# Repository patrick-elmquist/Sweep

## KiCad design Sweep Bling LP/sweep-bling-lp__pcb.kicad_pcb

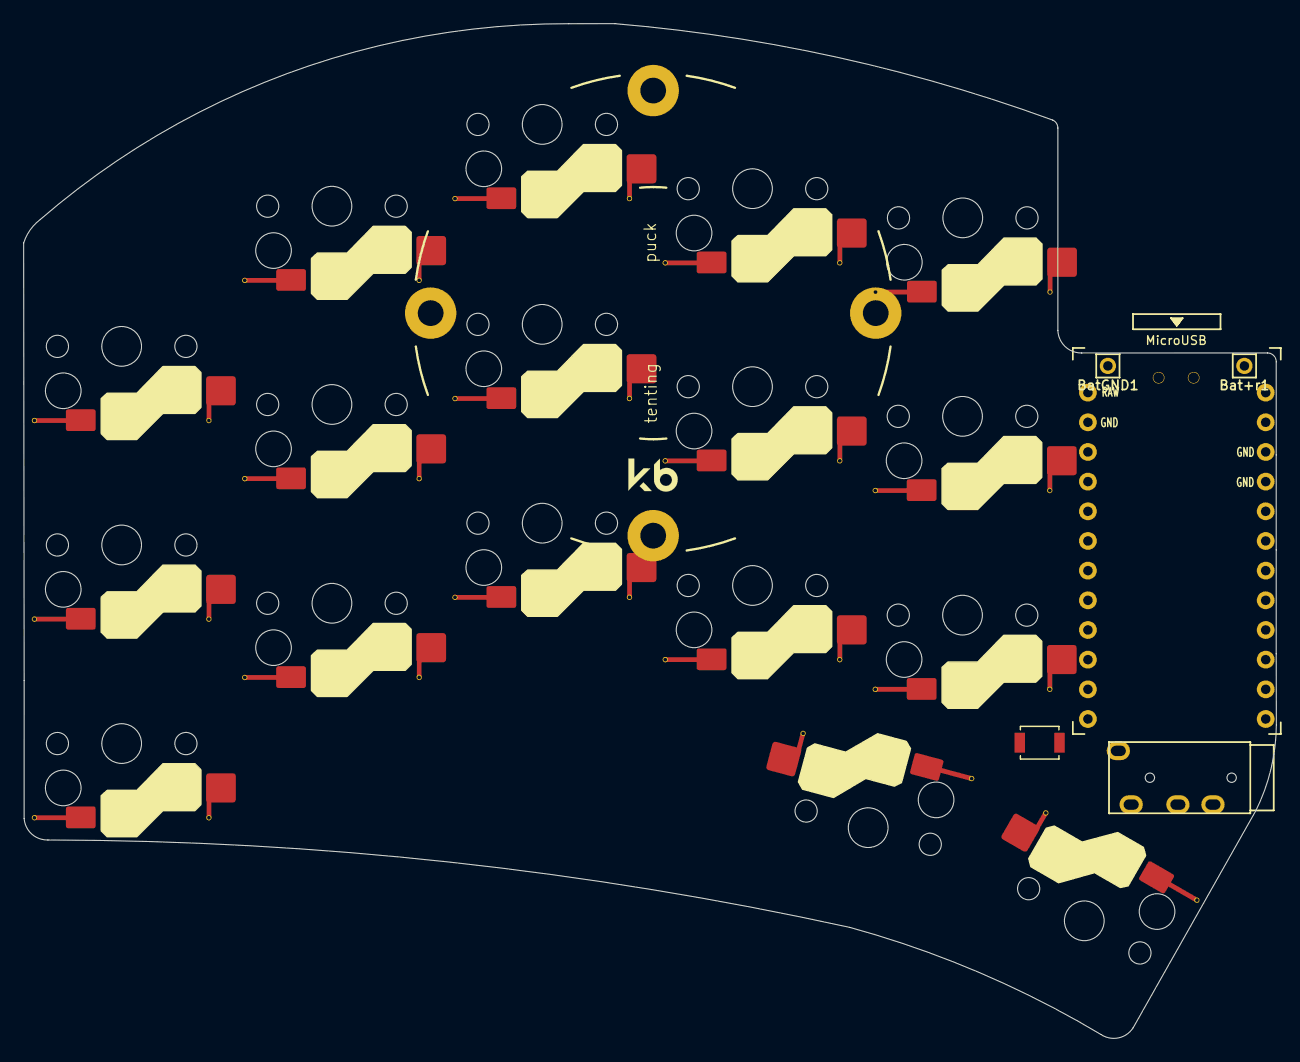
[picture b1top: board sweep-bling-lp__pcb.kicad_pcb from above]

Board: 2 copper layers, 107.2 x 86.9 mm, 23 parts (1 on the bottom side), 23 nets, no tracks yet.

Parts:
Bat+r1: MountingHole_Pad; 1pin_conn
BatGND1: MountingHole_Pad; 1pin_conn
J2: AudioJack4dpb; TRRS-PJ-320A
RSW1: SW_Push; SW_SPST_B3U-1000P
SW2, SW3, SW4, SW5, SW6, SW8, SW9, SW10, SW11, SW12, SW14, SW15, SW16, SW17, SW18, SW20, SW21: SW_Push; SW_Hotswap_Kailh_Choc_V1
SW_POWERR1: SW_SPDT; SPDT_C128955
U1: ProMicro-kbd; ProMicro_v3_min

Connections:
BT+_r: Bat+r1.1, SW_POWERR1.2
Switch1: SW2.1, U1.10
Switch2: SW3.1, U1.17
Switch3: SW4.1, U1.18
Switch4: SW5.1, U1.19
Switch5: SW6.1, U1.20
Switch6: SW8.1, U1.16
Switch7: SW9.1, U1.15
Switch8: SW10.1, U1.14
Switch9: SW11.1, U1.13
Switch10: SW12.1, U1.1
Switch11: SW14.1, U1.5
Switch12: SW15.1, U1.6
Switch13: SW16.1, U1.7
Switch14: SW17.1, U1.8
Switch15: SW18.1, U1.9
Switch16: SW21.1, U1.11
Switch17: SW20.1, U1.12
Switch18: J2.R1, U1.2
gnd: BatGND1.1, J2.S, J2.T, RSW1.1, SW2.2, SW3.2, SW4.2, SW5.2, SW6.2, SW8.2, SW9.2, SW10.2, SW11.2, SW12.2, SW14.2, SW15.2, SW16.2, SW17.2, SW18.2, SW20.2, SW21.2, U1.3, U1.4, U1.23
raw: SW_POWERR1.3, U1.24
reset: RSW1.2, U1.22
vcc: J2.R2, U1.21

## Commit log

2022-03-13 Create sweep bling lp
2022-04-23 [compact-low]: Fix silk, change reset button, update fills
2022-05-14 Added final pcb art
2022-05-14 Generated gerber
